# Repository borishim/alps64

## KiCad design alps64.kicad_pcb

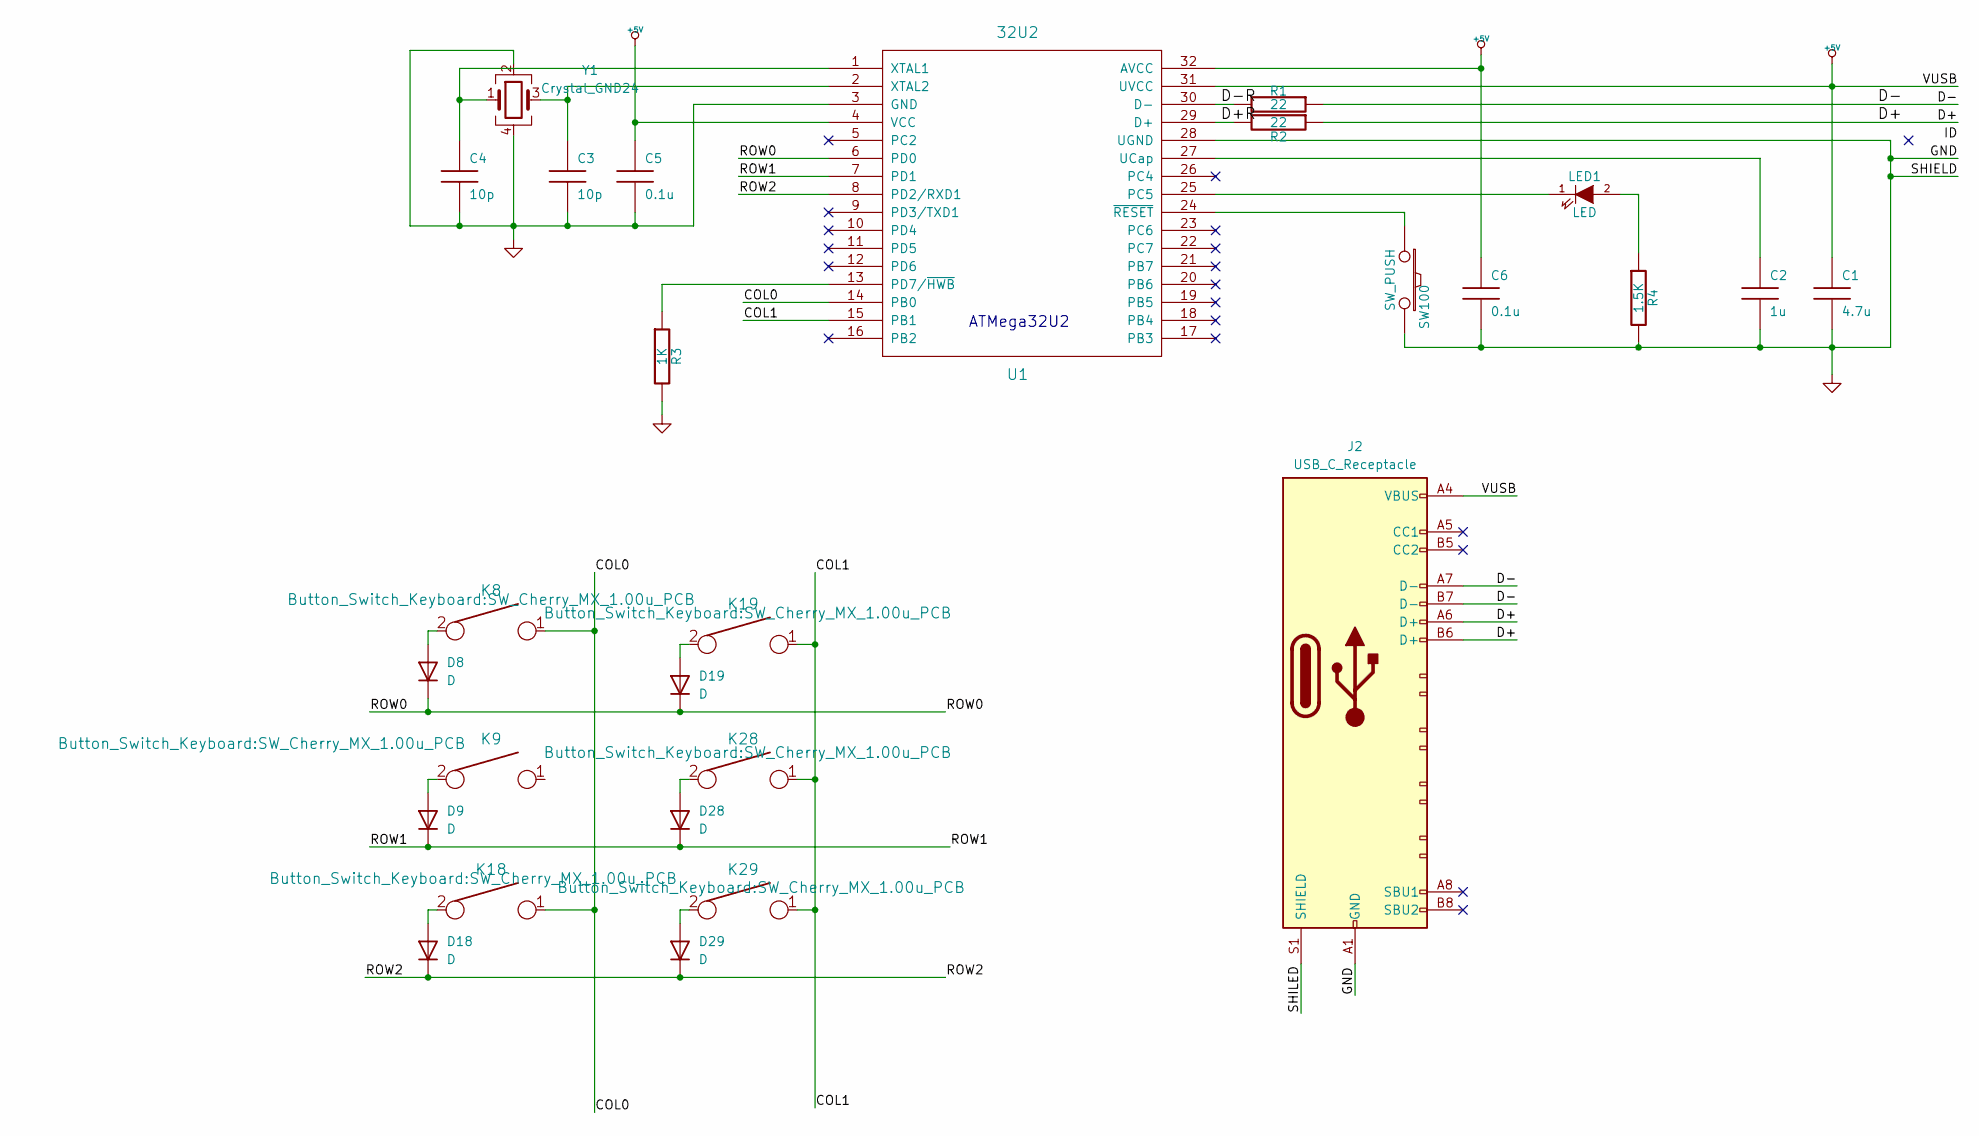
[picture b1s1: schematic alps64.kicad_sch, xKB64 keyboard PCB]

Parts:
C1: 4.7u; C_0603_1608Metric
C2: 1u; C_0603_1608Metric
C3, C4: 10p; C_0603_1608Metric
C5, C6: 0.1u; C_Disc_D3.0mm_W1.6mm_P2.50mm
D8, D9, D18, D19, D28, D29: D; D_SOD-323
J2: USB_C_Receptacle; USB_C_Receptacle_HCTL_HC-TYPE-C-16P-01A
K8, K9, K18, K19, K28, K29: keyboard_parts:KEYSW; SW_Cherry_MX_1.00u_PCB
LED1: LED; LED_D3.0mm
R1, R2: 22; R_0603_1608Metric
R3: 1K; R_0603_1608Metric
R4: 1.5K; R_0603_1608Metric
SW100: SW_PUSH; SW_PUSH_6mm
U1: 32U2; TQFP-32_7x7mm_P0.8mm
Y1: Crystal_GND24; Crystal_SMD_3225-4Pin_3.2x2.5mm

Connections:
+5V: C1.1, C5.1, C6.1, J2.A4 (VBUS), J2.A9 (VBUS), J2.B4 (VBUS), J2.B9 (VBUS), U1.4 (VCC), U1.31 (UVCC), U1.32 (AVCC)
/COL0: K8.1, K18.1, U1.14 (PB0)
/COL1: K19.1, K28.1, K29.1, U1.15 (PB1)
/D+: J2.A6 (D+), J2.B6 (D+), R2.1
/D+R: R2.2, U1.29 (D+)
/D-: J2.A7 (D-), J2.B7 (D-), R1.1
/D-R: R1.2, U1.30 (D-)
/ROW0: D8.1 (K), D19.1 (K), U1.6 (PD0)
/ROW1: D9.1 (K), D28.1 (K), U1.7 (PD1)
/ROW2: D18.1 (K), D29.1 (K), U1.8 (PD2/RXD1)
/SHILED: J2.S1 (SHIELD)
GND: C1.2, C2.2, C3.2, C4.2, C5.2, C6.2, J2.A1 (GND), J2.A12 (GND), J2.B1 (GND), J2.B12 (GND), R3.2, R4.2, SW100.2, U1.3 (GND), U1.28 (UGND), Y1.2, Y1.4
unnamed: D8.2 (A), K8.2
unnamed: D9.2 (A), K9.2
unnamed: D18.2 (A), K18.2
unnamed: D19.2 (A), K19.2
unnamed: D28.2 (A), K28.2
unnamed: D29.2 (A), K29.2
unnamed: LED1.2 (A), R4.1
unnamed: LED1.1 (K), U1.25 (PC5)
unnamed: R3.1, U1.13 (PD7/~HWB)
unnamed: C2.1, U1.27 (UCap)
unnamed: C4.1, U1.1 (XTAL1), Y1.1
unnamed: C3.1, U1.2 (XTAL2), Y1.3
unnamed: SW100.1, U1.24 (~RESET)

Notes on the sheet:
ATMega32U2

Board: 2 copper layers, 27 parts (0 on the bottom side), 24 nets, no tracks yet.

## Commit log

2023-12-28 Save the project files using Kicad 7
2023-12-28 Add keyboard footprints
2024-01-12 Update footprints
2024-01-12 Update wiring
2024-01-18 Update parts footprint
2024-01-18 Use through hall led footprint
